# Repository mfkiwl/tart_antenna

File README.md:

# TART Antenna

Author: Tim Molteno
License: GPL v3.0

This project is an active antenna design for the TART telescope. This goal of this project is to produce a PCB antenna with integrated Low Noise Amplifier (LNA) for the GPS L1 band (1575.42 MHz) where the TART telescope operates.

Ideally the antenna should have a radiation pattern that is well characterised. This will allow higher dynamic range images to be made. Other design factors can influence the array layout, for example it would be very helpful to have a model for how nearby antennas modify the radiation pattern (coupling between antennas).

## The LNA design

The LNA design uses an NXP GPS LNA chip which has a very good noise performance in the GPS band.

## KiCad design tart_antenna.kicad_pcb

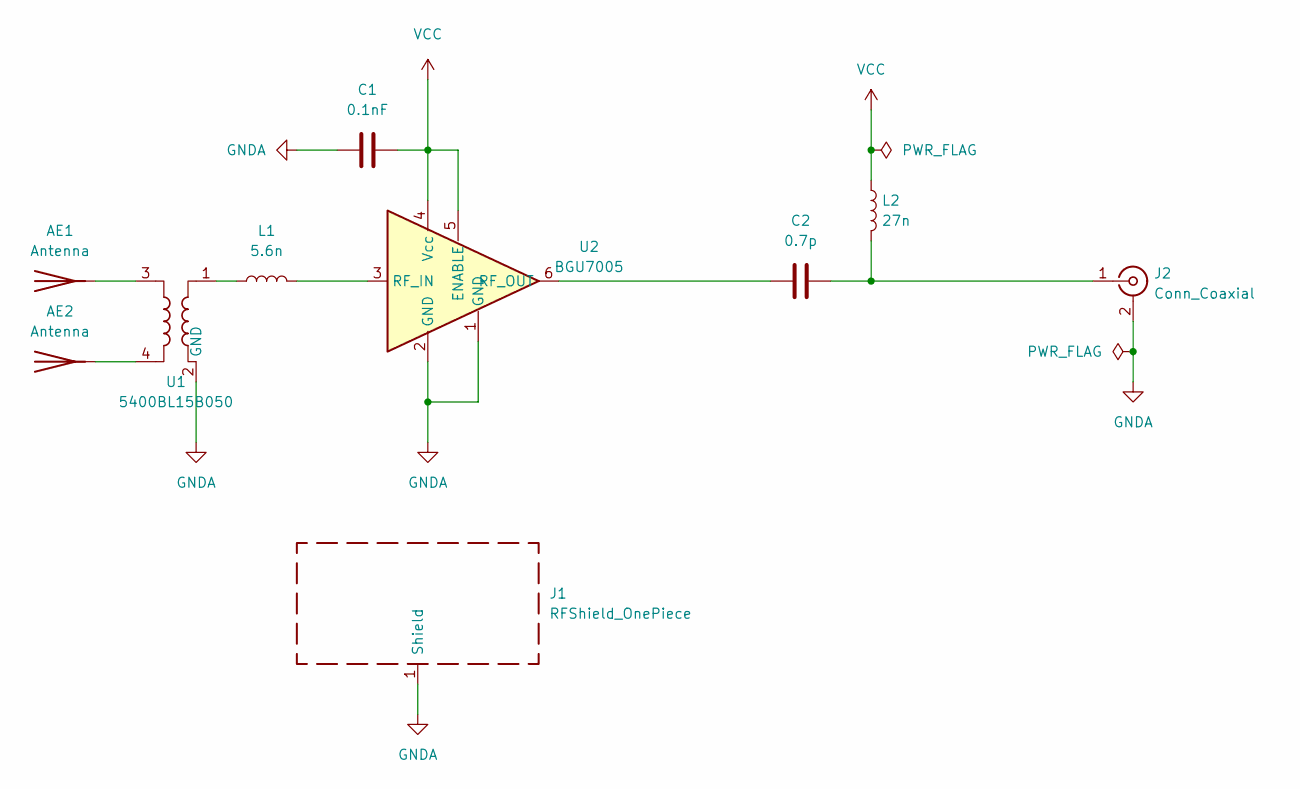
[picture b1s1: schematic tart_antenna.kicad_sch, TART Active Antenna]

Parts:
AE1, AE2: Antenna; TestPoint_Pad_D1.0mm
C1: 0.1nF; C_0402_1005Metric
C2: 0.7p; C_0402_1005Metric
J1: RFShield_OnePiece; Laird_Technologies_97-2003_12.70x13.37mm
J2: Conn_Coaxial; SMA_Amphenol_132134_Vertical
L1: 5.6n; L_0402_1005Metric; LCSC C91626
L2: 27n; L_0402_1005Metric; LCSC C12669
U1: 5400BL15B050; Balun_Johanson_5400BL15B050E
U2: BGU7005; SOT-886; LCSC C38438

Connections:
GNDA: C1.1, J1.1 (Shield), J2.2 (Ext), U1.2 (GND), U1.5 (GND), U2.1 (GND), U2.2 (GND)
unnamed: AE1.1 (A), U1.3
unnamed: AE2.1 (A), U1.4
unnamed: C2.1, U2.6 (RF_OUT)
unnamed: C2.2, J2.1 (In), L2.2
unnamed: L1.1, U1.1
unnamed: L1.2, U2.3 (RF_IN)
VCC: C1.2, L2.1, U2.4 (Vcc), U2.5 (ENABLE)

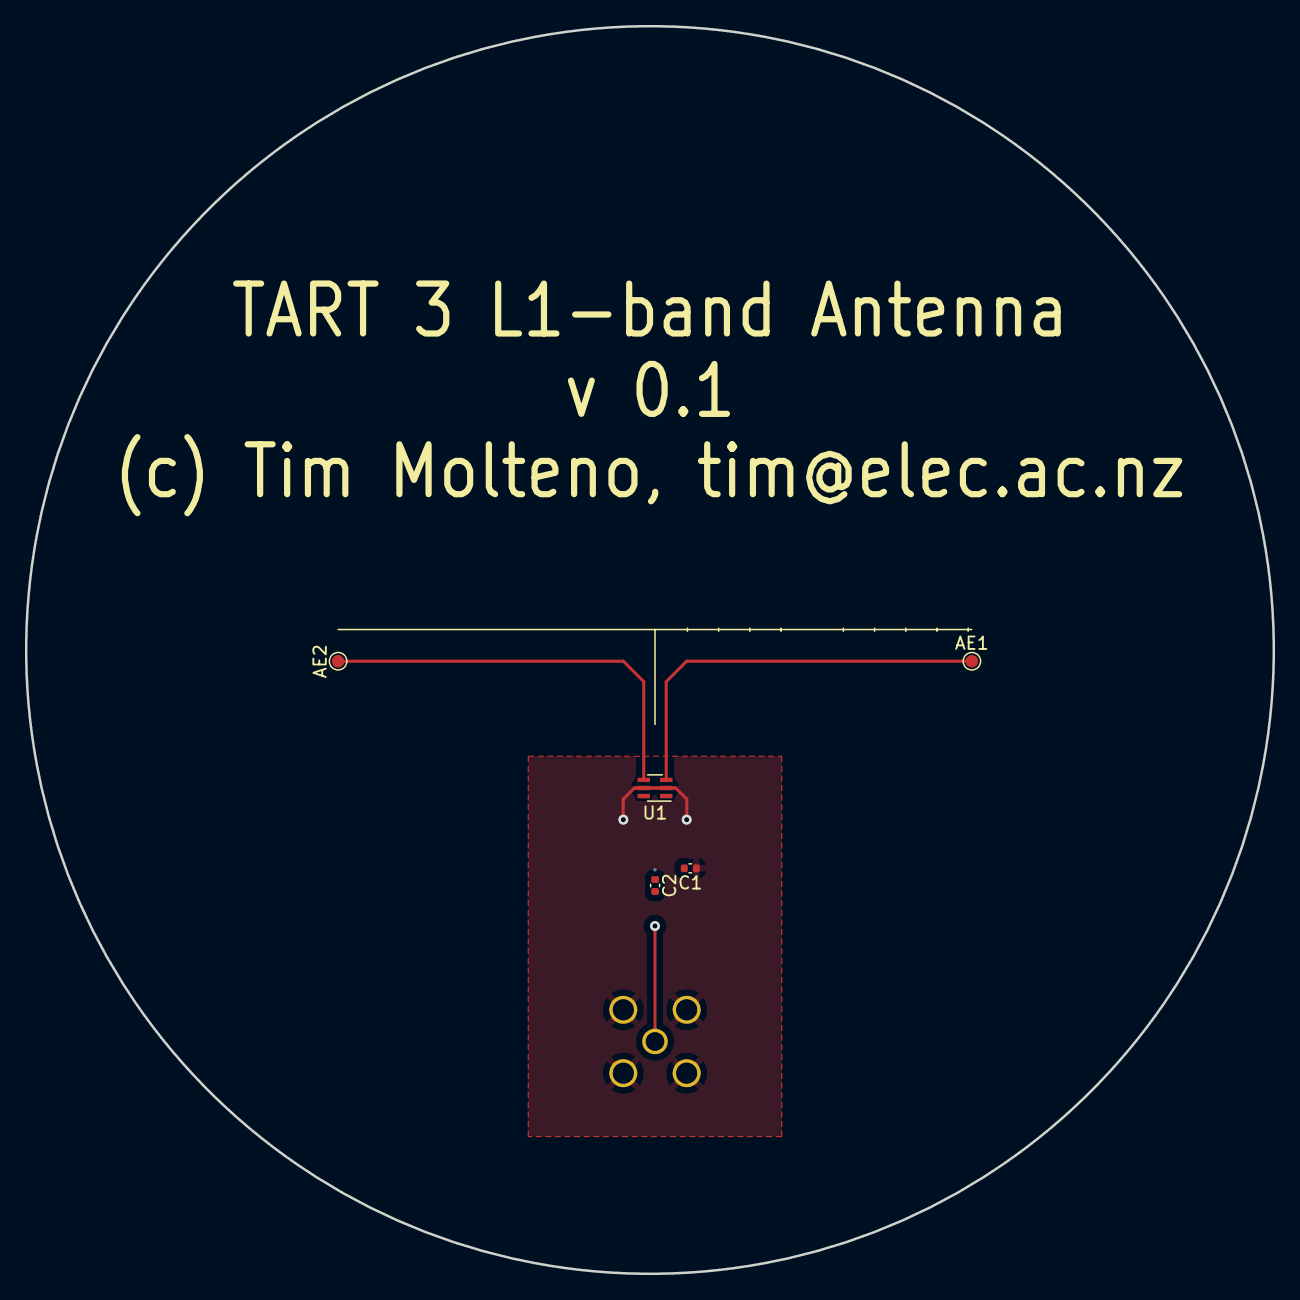
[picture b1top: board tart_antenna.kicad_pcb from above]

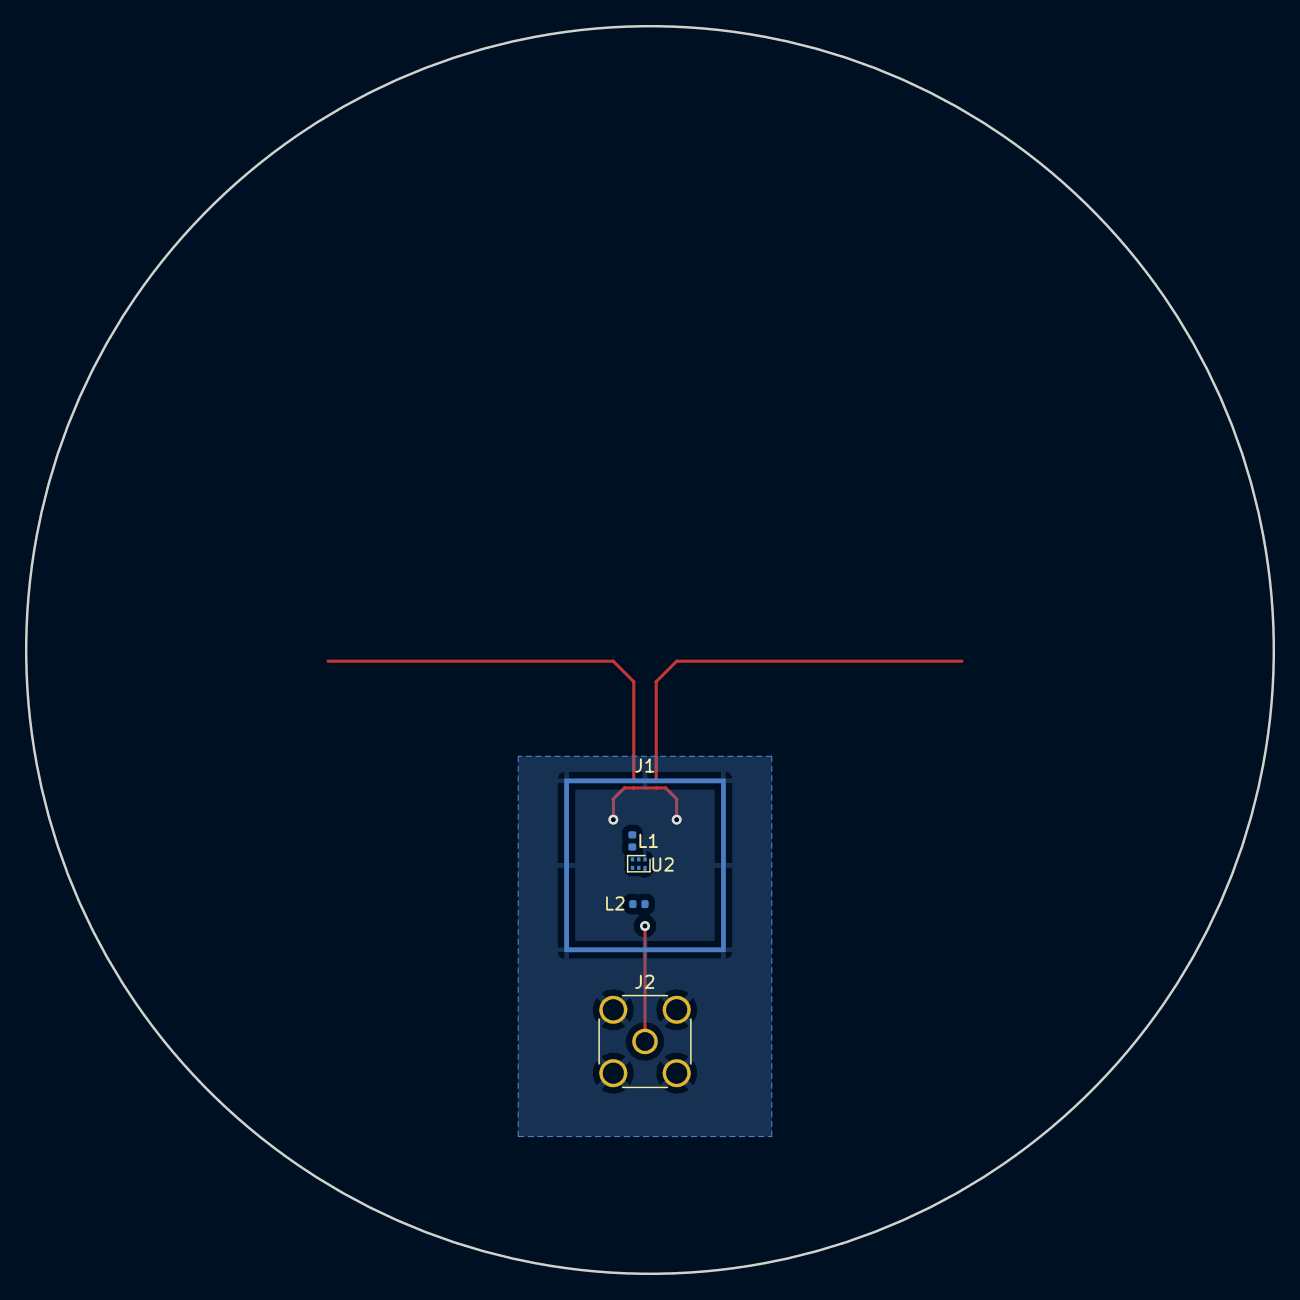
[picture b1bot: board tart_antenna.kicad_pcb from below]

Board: 6 copper layers, 100.0 x 100.0 mm, 10 parts (5 on the bottom side), 8 nets.

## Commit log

2022-09-15 Add author and license
2022-09-15 Added sheet template
2023-01-31 Change PCB stack
2023-07-18 Added ground disk
2023-07-18 Add grid of holes for drainage
2024-07-31 Added round background
2024-08-02 TART_PCB_Antenna_V1
    Version 1 of the TART PCB Patch antenna
2024-08-02 TART Passive Antenna
    2 Layer 1.6mm passive patch antenna for the Transient Array Radio Telescope
2024-08-02 stackup added
    stackup added
2024-09-15 Reduced dimensions, and increased hole size to lighten disk
